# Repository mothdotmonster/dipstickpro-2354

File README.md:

# DIPSTICKPRO 2354

pro micro sized, with all the features i wanted from other similar sized things

put python on it: https://github.com/mothdotmonster/circuitpython/releases

## pinout

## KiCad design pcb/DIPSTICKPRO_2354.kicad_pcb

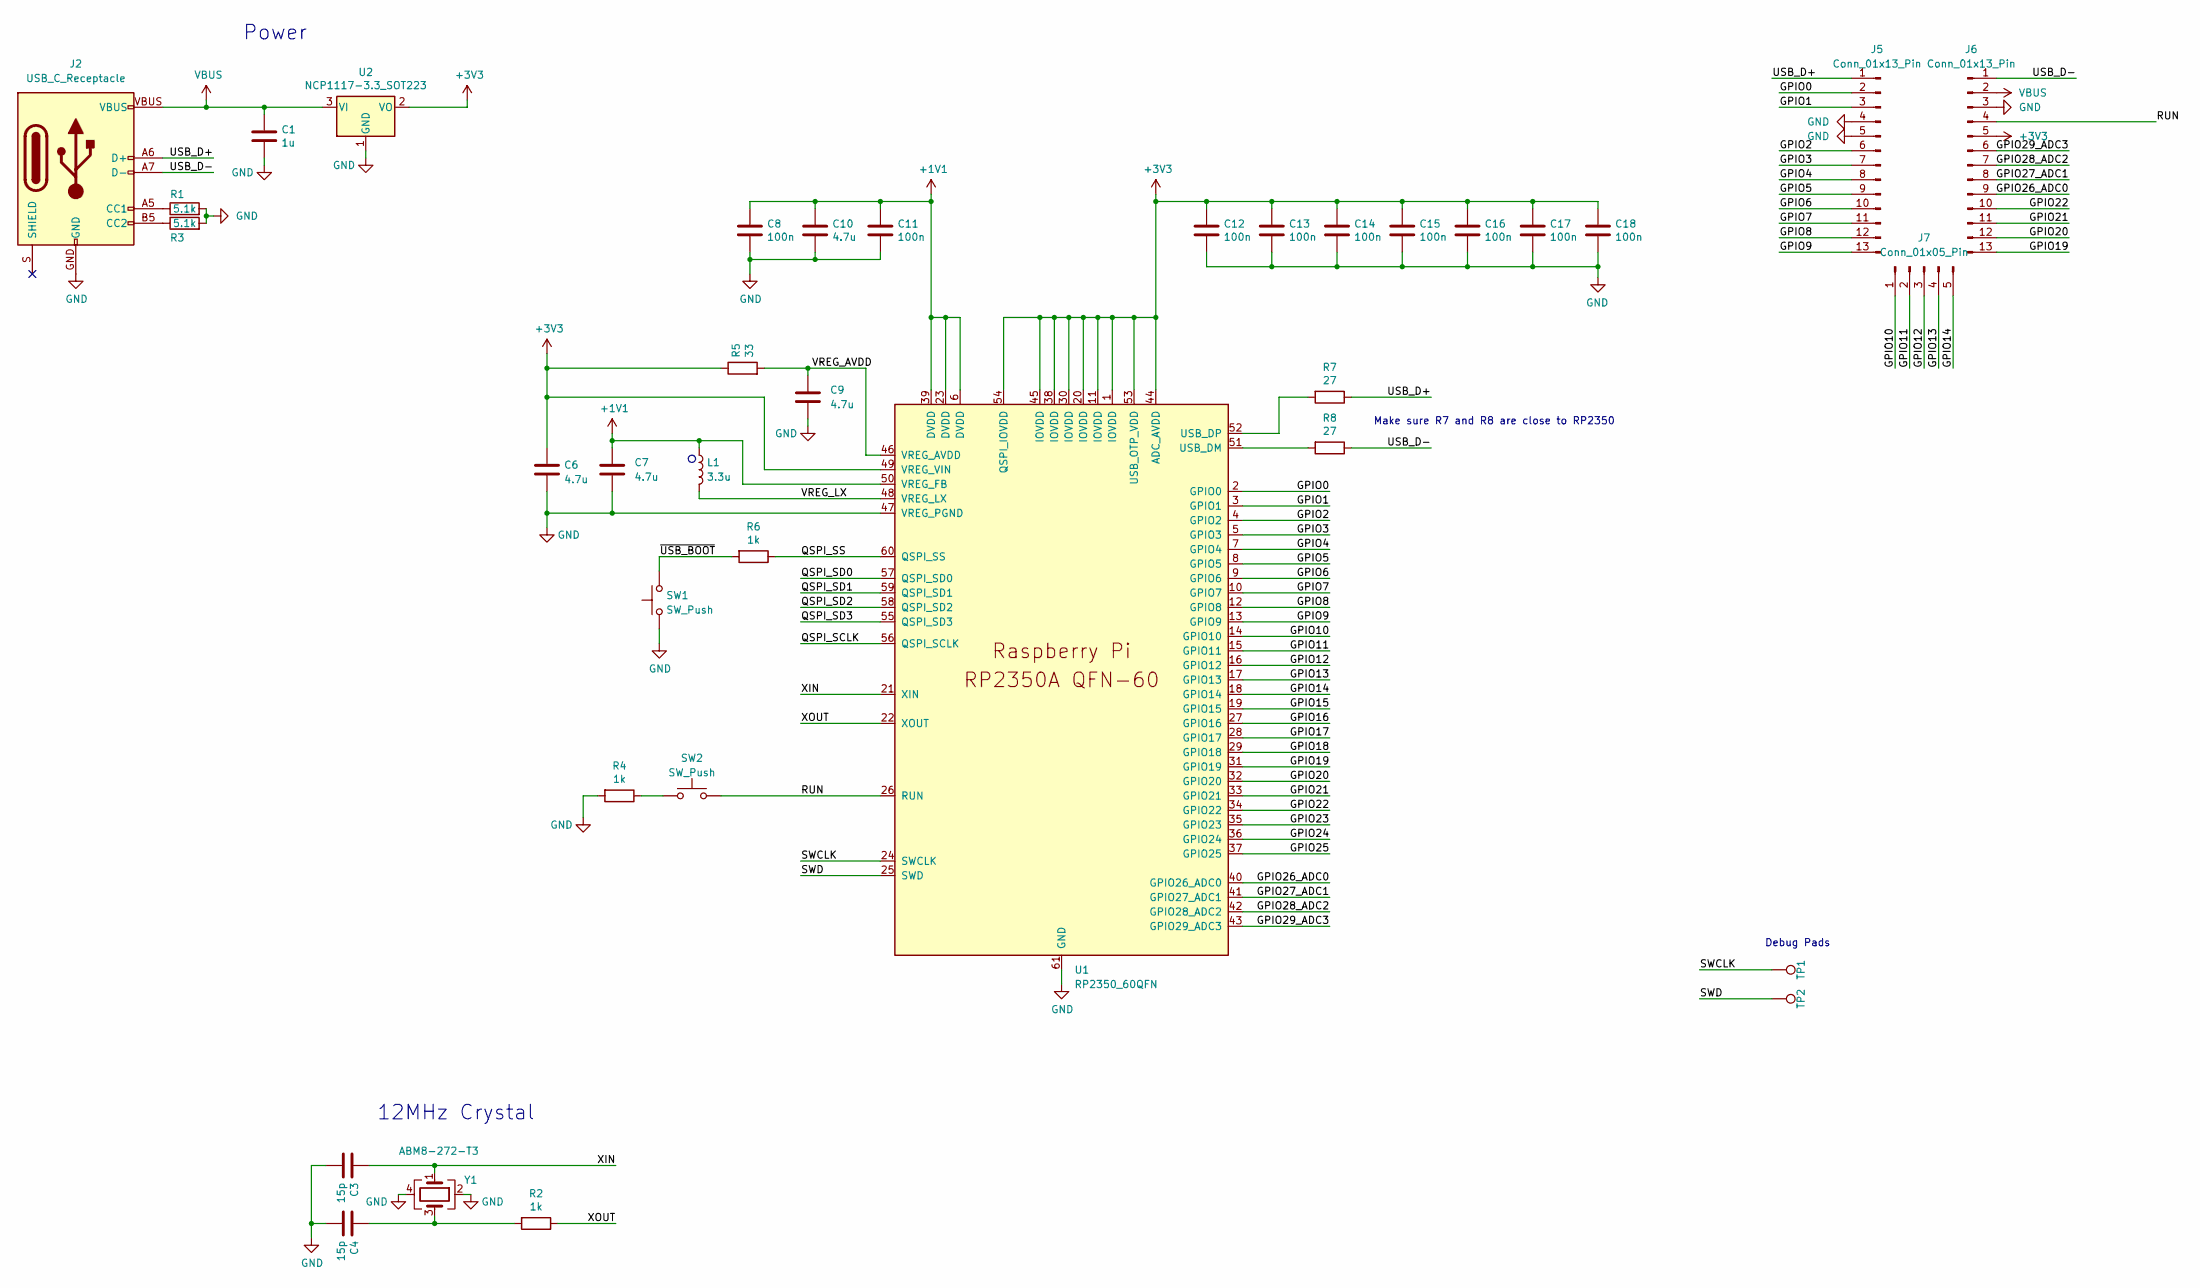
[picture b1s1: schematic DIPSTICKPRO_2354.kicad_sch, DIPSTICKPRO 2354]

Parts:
C1: 1u; C_0402_1005Metric
C3, C4: 15p; C_0402_1005Metric
C6, C7: 4.7u; C_0402_1005Metric_small_pads
C8, C11, C12, C13, C14, C15, C16, C17, C18: 100n; C_0402_1005Metric
C9, C10: 4.7u; C_0402_1005Metric
J2: USB_C_Receptacle; USB-C_16
J5, J6: Conn_01x13_Pin; 1x12_P2.54mm_Castellated
J7: Conn_01x05_Pin; 1x05_P2.54mm_Castellated
L1: 3.3u; L_pol_2016
R1, R3: 5.1k; R_0402_1005Metric; LCSC C25905
R2, R4, R6: 1k; R_0402_1005Metric
R5: 33; R_0402_1005Metric
R7, R8: 27; R_0402_1005Metric
SW1, SW2: SW_Push; SW_SPST_TS-1088-xR020
TP1, TP2: 0.5mm; TestPoint-0.5mm
U1: RP2350_60QFN; RP2350-QFN-60-1EP_7x7_P0.4mm_EP3.4x3.4mm_ThermalVias
U2: NCP1117-3.3_SOT223; SOT-23-3; JLC C5446
Y1: ABM8-272-T3; Crystal_SMD_3225-4Pin_3.2x2.5mm

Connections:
+1V1: C7.1, C8.1, C10.1, C11.1, L1.1, U1.6 (DVDD), U1.23 (DVDD), U1.39 (DVDD), U1.50 (VREG_FB)
+3V3: C6.1, C12.1, C13.1, C14.1, C15.1, C16.1, C17.1, C18.1, J6.5, R5.1, U1.1 (IOVDD), U1.11 (IOVDD), U1.20 (IOVDD), U1.30 (IOVDD), U1.38 (IOVDD), U1.44 (ADC_AVDD), U1.45 (IOVDD), U1.49 (VREG_VIN), U1.53 (USB_OTP_VDD), U1.54 (QSPI_IOVDD), U2.2 (VO)
/GPIO0: J5.2, U1.2 (GPIO0)
/GPIO1: J5.3, U1.3 (GPIO1)
/GPIO2: J5.6, U1.4 (GPIO2)
/GPIO3: J5.7, U1.5 (GPIO3)
/GPIO4: J5.8, U1.7 (GPIO4)
/GPIO5: J5.9, U1.8 (GPIO5)
/GPIO6: J5.10, U1.9 (GPIO6)
/GPIO7: J5.11, U1.10 (GPIO7)
/GPIO8: J5.12, U1.12 (GPIO8)
/GPIO9: J5.13, U1.13 (GPIO9)
/GPIO10: J7.1, U1.14 (GPIO10)
/GPIO11: J7.2, U1.15 (GPIO11)
/GPIO12: J7.3, U1.16 (GPIO12)
/GPIO13: J7.4, U1.17 (GPIO13)
/GPIO14: J7.5, U1.18 (GPIO14)
/GPIO15: U1.19 (GPIO15)
/GPIO16: U1.27 (GPIO16)
/GPIO17: U1.28 (GPIO17)
/GPIO18: U1.29 (GPIO18)
/GPIO19: J6.13, U1.31 (GPIO19)
/GPIO20: J6.12, U1.32 (GPIO20)
/GPIO21: J6.11, U1.33 (GPIO21)
/GPIO22: J6.10, U1.34 (GPIO22)
/GPIO23: U1.35 (GPIO23)
/GPIO24: U1.36 (GPIO24)
/GPIO25: U1.37 (GPIO25)
/GPIO26_ADC0: J6.9, U1.40 (GPIO26_ADC0)
/GPIO27_ADC1: J6.8, U1.41 (GPIO27_ADC1)
/GPIO28_ADC2: J6.7, U1.42 (GPIO28_ADC2)
/GPIO29_ADC3: J6.6, U1.43 (GPIO29_ADC3)
/QSPI_SCLK: U1.56 (QSPI_SCLK)
/QSPI_SD0: U1.57 (QSPI_SD0)
/QSPI_SD1: U1.59 (QSPI_SD1)
/QSPI_SD2: U1.58 (QSPI_SD2)
/QSPI_SD3: U1.55 (QSPI_SD3)
/QSPI_SS: R6.1, U1.60 (QSPI_SS)
/RUN: J6.4, SW2.2, U1.26 (RUN)
/SWCLK: TP1.1, U1.24 (SWCLK)
/SWD: TP2.1, U1.25 (SWD)
/USB_D+: J2.A6 (D+), J2.B6 (D+), J5.1, R7.1
/USB_D-: J2.A7 (D-), J2.B7 (D-), J6.1, R8.1
/VREG_AVDD: C9.1, R5.2, U1.46 (VREG_AVDD)
/VREG_LX: L1.2, U1.48 (VREG_LX)
/XIN: C3.1, U1.21 (XIN), Y1.1
/XOUT: R2.1, U1.22 (XOUT)
/~USB_BOOT: R6.2, SW1.2
GND: C1.2, C3.2, C4.2, C6.2, C7.2, C8.2, C9.2, C10.2, C11.2, C12.2, C13.2, C14.2, C15.2, C16.2, C17.2, C18.2, J2.GND, J5.4, J5.5, J6.3, R1.2, R3.2, R4.2, SW1.1, U1.47 (VREG_PGND), U1.61 (GND), U2.1 (GND), Y1.2, Y1.4
unnamed: C4.1, R2.2, Y1.3
unnamed: J2.A5 (CC1), R1.1
unnamed: J2.B5 (CC2), R3.1
unnamed: R4.1, SW2.1
unnamed: R8.2, U1.51 (USB_DM)
unnamed: R7.2, U1.52 (USB_DP)
VBUS: C1.1, J2.VBUS, J6.2, U2.3 (VI)

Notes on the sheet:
Debug Pads
Make sure R7 and R8 are close to RP2350
12MHz Crystal
Power

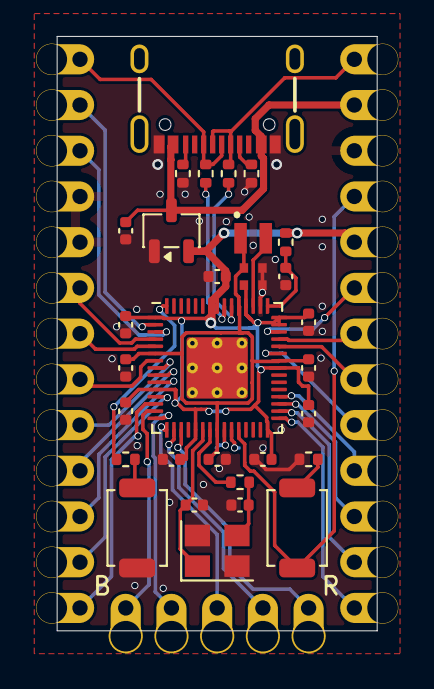
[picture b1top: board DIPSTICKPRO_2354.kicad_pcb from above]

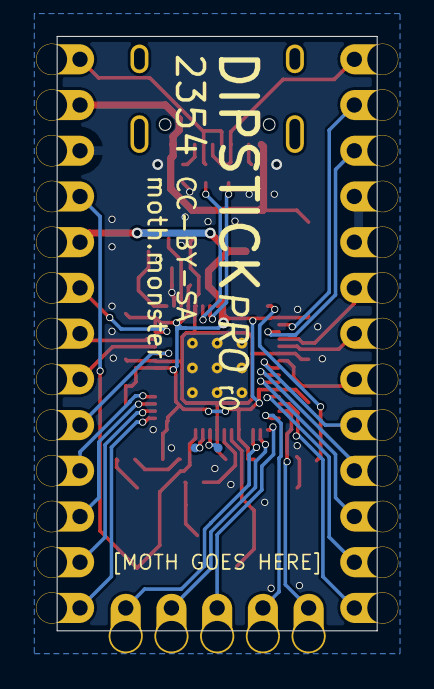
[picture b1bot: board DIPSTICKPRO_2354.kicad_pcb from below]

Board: 2 copper layers, 17.8 x 33.0 mm, 36 parts (4 on the bottom side), 44 nets.

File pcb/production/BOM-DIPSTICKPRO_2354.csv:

Comment,Designator,Footprint,LCSC,Quantity
100n,"C11,C12,C13,C14,C15,C16,C17,C18,C8",C_0402_1005Metric,C1525,9
15p,"C3,C4",C_0402_1005Metric,C1548,2
1k,"R2,R4,R6",R_0402_1005Metric,C11702,3
1u,C1,C_0402_1005Metric,C52923,1
27,"R7,R8",R_0402_1005Metric,C25092,2
3.3u,L1,L_pol_2016,C42411119,1
33,R5,R_0402_1005Metric,C25105,1
4.7u,"C10,C6,C7,C9",C_0402_1005Metric,C23733,4
5.1k,"R1,R3",R_0402_1005Metric,C25905,2
ABM8-272-T3,Y1,Crystal_SMD_3225-4Pin_3.2x2.5mm,C20625731,1
NCP1117-3.3_SOT223,U2,SOT-23-3,C5446,1
RP2350_60QFN,U1,RP2350-QFN-60-1EP_7x7_P0.4mm_EP3.4x3.4mm_ThermalVias,C41378174,1
SW_Push,"SW1,SW2",SW_SPST_TS-1088-xR020,C720477,2
USB_C_Receptacle,J2,USB-C_16,C165948,1

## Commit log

2026-01-30 add pinout

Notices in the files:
pcb/DIPSTICKPRO_2354.kicad_pcb:
CC-BY-SA
